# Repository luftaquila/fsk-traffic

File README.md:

# Formula Student Korea Traffic Controller

## Development

### Controller firmware

#### Prerequisites

```sh
git clone https://github.com/luftaquila/fsk-traffic.git
```

* `arm-none-eabi-gcc` ([AArch32 bare-metal target (arm-none-eabi)](https://developer.arm.com/downloads/-/arm-gnu-toolchain-downloads))
* make
* openocd

#### Build and upload

```sh
cd device/firmware
make program
```

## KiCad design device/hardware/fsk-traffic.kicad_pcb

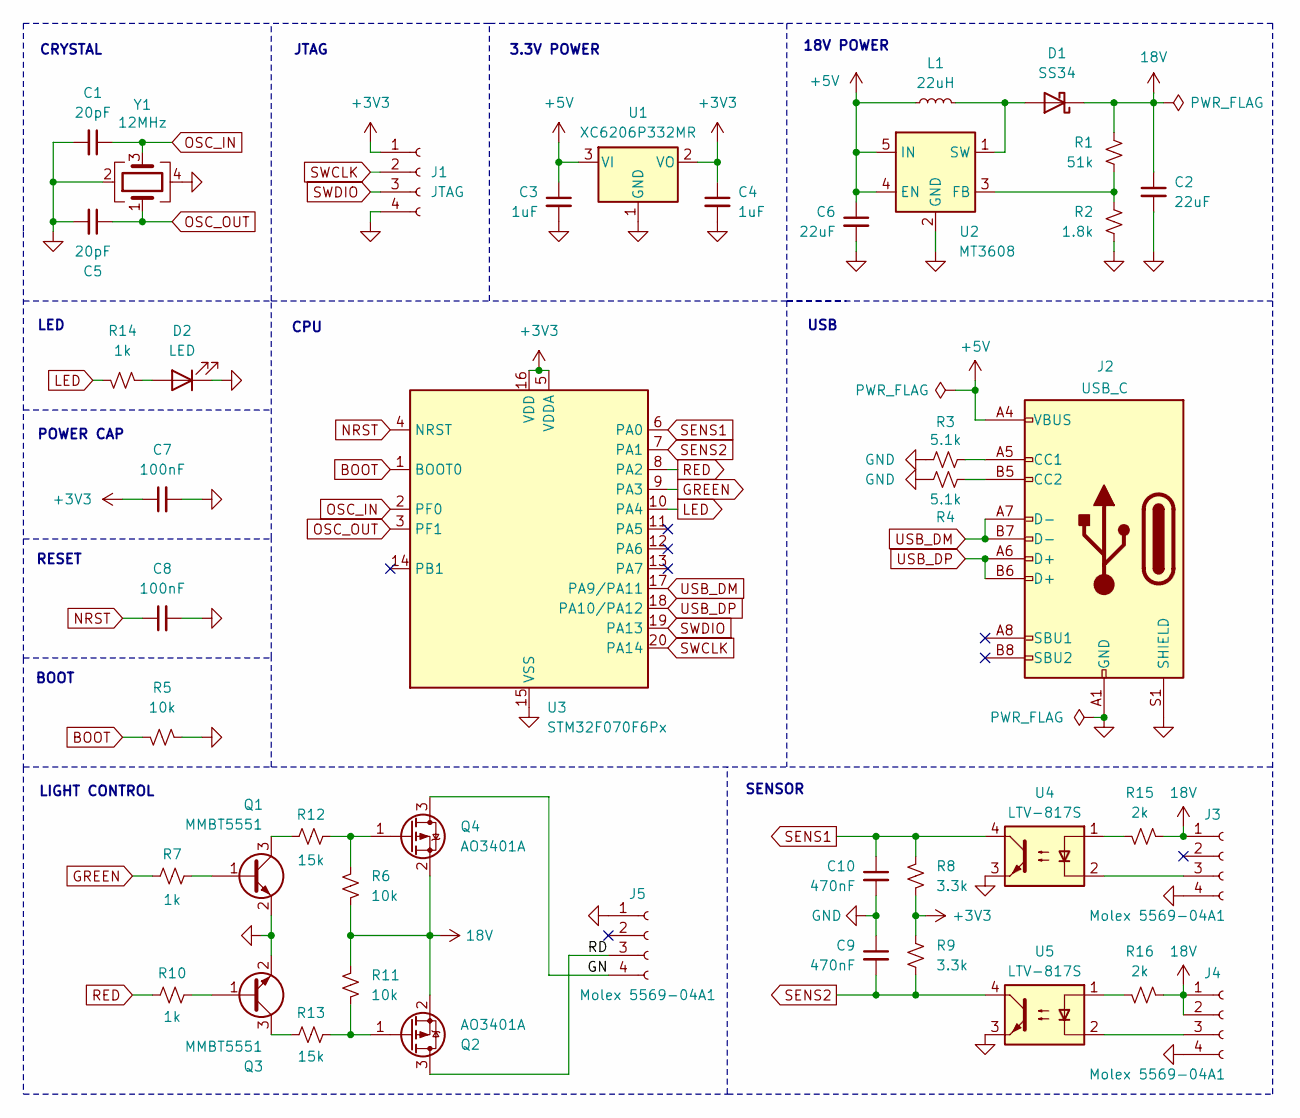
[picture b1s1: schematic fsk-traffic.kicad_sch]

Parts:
C1, C5: 20pF; C_0603_1608Metric; LCSC C1648
C2, C6: 22uF; C_0805_2012Metric; LCSC C45783
C3, C4: 1uF; C_0603_1608Metric; LCSC C15849
C7, C8: 100nF; C_0603_1608Metric; LCSC C14663
C9, C10: 470nF; C_0603_1608Metric; LCSC C1623
D1: SS34; D_SMA; LCSC C8678
D2: LED; LED_0603_1608Metric; LCSC C2286
J1: JTAG; PinHeader_1x04_P2.54mm_Vertical
J2: USB_C; USB_C_Receptacle_GCT_USB4105-xx-A_16P_TopMnt_Horizontal; LCSC C165948
J3, J4, J5: Molex 5569-04A1; Molex_Mini-Fit_Jr_5569-04A1_2x02_P4.20mm_Horizontal
L1: 22uH; L_Changjiang_FXL0630; LCSC C177244
Q1, Q3: MMBT5551; SOT-23; LCSC C2145
Q2, Q4: AO3401A; SOT-23; LCSC C15127
R1: 51k; R_0603_1608Metric; LCSC C23196
R2: 1.8k; R_0603_1608Metric; LCSC C4177
R3, R4: 5.1k; R_0603_1608Metric; LCSC C23186
R5, R6, R11: 10k; R_0603_1608Metric; LCSC C25804
R7, R10, R14: 1k; R_0603_1608Metric; LCSC C21190
R8, R9: 3.3k; R_0603_1608Metric; LCSC C22978
R12, R13: 15k; R_0603_1608Metric; LCSC C22809
R15, R16: 2k; R_0603_1608Metric; LCSC C22975
U1: XC6206P332MR; SOT-23-3; LCSC C5446
U2: MT3608; SOT-23-6; LCSC C2932326
U3: STM32F070F6Px; TSSOP-20_4.4x6.5mm_P0.65mm; LCSC C86951
U4, U5: LTV-817S; SMDIP-4_W9.53mm; LCSC C109227
Y1: 12MHz; Crystal_SMD_3225-4Pin_3.2x2.5mm; LCSC C9002

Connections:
18V: C2.1, D1.1 (K), J3.1, J4.1, J4.2, Q2.2 (S), Q4.2 (S), R1.1, R6.2, R11.1, R15.1, R16.1
+3V3: C4.1, C7.1, J1.1, R8.2, R9.1, U1.2 (VO), U3.5 (VDDA), U3.16 (VDD)
+5V: C3.1, C6.1, J2.A4 (VBUS), J2.A9 (VBUS), J2.B4 (VBUS), J2.B9 (VBUS), L1.1, U1.3 (VI), U2.4 (EN), U2.5 (IN)
/GN: J5.4, Q4.3 (D)
/RD: J5.3, Q2.3 (D)
BOOT: R5.2, U3.1 (BOOT0)
GND: C1.2, C2.2, C3.2, C4.2, C5.2, C6.2, C7.2, C8.2, C9.1, C10.2, D2.1 (K), J1.4, J2.A1 (GND), J2.A12 (GND), J2.B1 (GND), J2.B12 (GND), J2.S1 (SHIELD), J3.4, J4.4, J5.1, Q1.2 (E), Q3.2 (E), R2.2, R3.1, R4.1, R5.1, U1.1 (GND), U2.2 (GND), U3.15 (VSS), U4.3, U5.3, Y1.2, Y1.4
GREEN: R7.2, U3.9 (PA3)
LED: R14.2, U3.10 (PA4)
NRST: C8.1, U3.4 (NRST)
unnamed: D1.2 (A), L1.2, U2.1 (SW)
unnamed: D2.2 (A), R14.1
unnamed: J2.A5 (CC1), R3.2
unnamed: J2.B5 (CC2), R4.2
unnamed: J3.3, U4.2
unnamed: J4.3, U5.2
unnamed: Q1.1 (B), R7.1
unnamed: Q1.3 (C), R12.2
unnamed: Q2.1 (G), R11.2, R13.1
unnamed: Q3.1 (B), R10.1
unnamed: Q3.3 (C), R13.2
unnamed: Q4.1 (G), R6.1, R12.1
unnamed: R15.2, U4.1
unnamed: R16.2, U5.1
unnamed: R1.2, R2.1, U2.3 (FB)
OSC_IN: C1.1, U3.2 (PF0), Y1.3
OSC_OUT: C5.1, U3.3 (PF1), Y1.1
RED: R10.2, U3.8 (PA2)
SENS1: C10.1, R8.1, U3.6 (PA0), U4.4
SENS2: C9.2, R9.2, U3.7 (PA1), U5.4
SWCLK: J1.2, U3.20 (PA14)
SWDIO: J1.3, U3.19 (PA13)
USB_DM: J2.A7 (D-), J2.B7 (D-), U3.17 (PA9/PA11)
USB_DP: J2.A6 (D+), J2.B6 (D+), U3.18 (PA10/PA12)

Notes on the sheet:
SENSOR
3.3V POWER
LIGHT CONTROL
POWER CAP
CPU
JTAG
18V POWER
RESET
BOOT
LED
CRYSTAL
USB

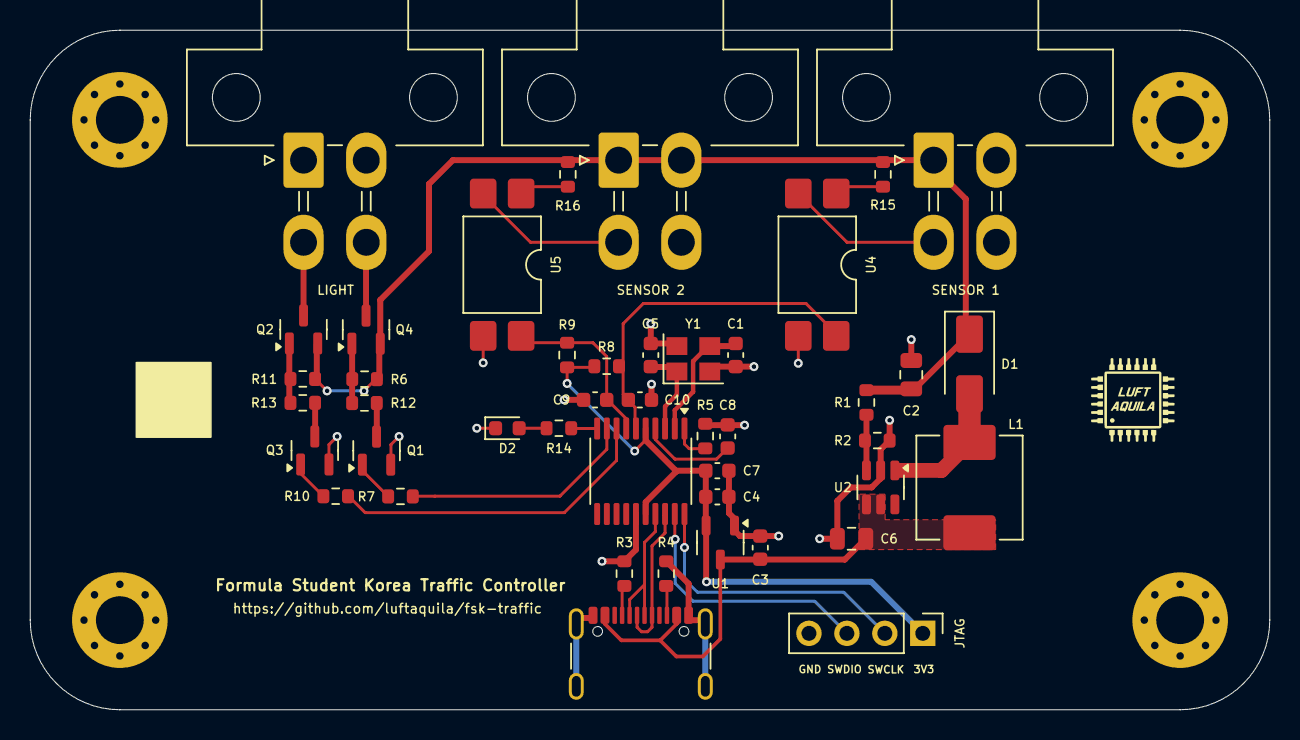
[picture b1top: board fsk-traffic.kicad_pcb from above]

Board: 2 copper layers, 83.0 x 45.5 mm, 44 parts (0 on the bottom side), 34 nets.

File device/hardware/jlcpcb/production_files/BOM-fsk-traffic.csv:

Comment,Designator,Footprint,LCSC,Quantity
LTV-817S,"U4,U5",SMDIP-4_W9.53mm,C109227,2
100nF,"C7,C8",C_0603_1608Metric,C14663,2
AO3401A,"Q2,Q4",SOT-23,C15127,2
1uF,"C3,C4",C_0603_1608Metric,C15849,2
470nF,"C10,C9",C_0603_1608Metric,C1623,2
20pF,"C1,C5",C_0603_1608Metric,C1648,2
USB_C,J2,USB_C_Receptacle_GCT_USB4105-xx-A_16P_TopMnt_Horizontal,C165948,1
22uH,L1,L_Changjiang_FXL0630,C177244,1
1k,"R10,R14,R7",R_0603_1608Metric,C21190,3
MMBT5551,"Q1,Q3",SOT-23,C2145,2
15k,"R12,R13",R_0603_1608Metric,C22809,2
LED,D2,LED_0603_1608Metric,C2286,1
2k,"R15,R16",R_0603_1608Metric,C22975,2
3.3k,"R8,R9",R_0603_1608Metric,C22978,2
5.1k,"R3,R4",R_0603_1608Metric,C23186,2
51k,R1,R_0603_1608Metric,C23196,1
10k,"R11,R5,R6",R_0603_1608Metric,C25804,3
1.8k,R2,R_0603_1608Metric,C4177,1
22uF,"C2,C6",C_0805_2012Metric,C45783,2
XC6206P332MR,U1,SOT-23-3,C5446,1
SS34,D1,D_SMA,C8678,1
STM32F070F6Px,U3,TSSOP-20_4.4x6.5mm_P0.65mm,C86951,1
12MHz,Y1,Crystal_SMD_3225-4Pin_3.2x2.5mm,C9002,1
MT3608,U2,SOT-23-6,,1

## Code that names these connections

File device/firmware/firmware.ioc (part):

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Mcu.Name=STM32F070F6Px
Mcu.Package=TSSOP20
Mcu.UserName=STM32F070F6Px
PA0.GPIOParameters=GPIO_Label,GPIO_ModeDefaultEXTI
PA0.GPIO_Label=SENS1
PA0.GPIO_ModeDefaultEXTI=GPIO_MODE_IT_FALLING
PA0.Signal=GPXTI0
PA1.GPIOParameters=GPIO_Label,GPIO_ModeDefaultEXTI
PA1.GPIO_Label=SENS2
PA1.GPIO_ModeDefaultEXTI=GPIO_MODE_IT_FALLING
PA1.Signal=GPXTI1
PA11.Mode=Device
PA11.Signal=USB_DM
PA12.Mode=Device
PA12.Signal=USB_DP
PA13.Mode=Serial_Wire
PA13.Signal=SYS_SWDIO
PA14.Mode=Serial_Wire
PA14.Signal=SYS_SWCLK
PA2.GPIOParameters=GPIO_Label
PA2.GPIO_Label=RED
PA2.Signal=GPIO_Output
PA3.GPIOParameters=GPIO_Label
PA3.GPIO_Label=GREEN
PA3.Signal=GPIO_Output
PA4.GPIOParameters=GPIO_PuPd,GPIO_Label,GPIO_ModeDefaultOutputPP
PA4.GPIO_Label=LED
PA4.GPIO_ModeDefaultOutputPP=GPIO_MODE_OUTPUT_PP
PA4.GPIO_PuPd=GPIO_NOPULL
PA4.Signal=GPIO_Output
PF0-OSC_IN.Mode=HSE-External-Oscillator
PF0-OSC_IN.Signal=RCC_OSC_IN
PF1-OSC_OUT.Mode=HSE-External-Oscillator
PF1-OSC_OUT.Signal=RCC_OSC_OUT
RCC.HSE_VALUE=12000000
RCC.SYSCLKFreq_VALUE=48000000
RCC.SYSCLKSource=RCC_SYSCLKSOURCE_PLLCLK
board=custom

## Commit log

2025-03-12 remove: sensor firmware
2025-03-16 update: set sensor input pins
2025-03-18 update: new firmware with wired sensors
2025-03-18 fix: make cmds
2025-03-18 improve: fixed length usb cmd
2025-03-18 fix: usb recv flag
2025-03-18 fix: sensor detection bugs
2025-03-18 add: 200ms debouncing
2025-03-23 refactor: UI structure
2025-03-23 fix: misc UI bugs
2025-03-23 impl: main race logic
2025-03-23 update: exclude linux build from release
2025-03-23 impl: save records
2025-03-23 update: readme
2025-03-23 update: beerware license
2025-03-23 add: schematics
2025-04-01 update: match mode name to actual name
2025-04-01 add: skidpad mode UI
2025-04-02 impl: skidpad mode
2025-04-02 add: record save tips
2025-04-05 update: misc style
2025-04-05 update: drop native
2025-04-05 impl: serial handler and POST fetch
2025-04-05 rename: fsk-traffic-control to fsk-traffic
2025-04-05 add: initial server container structure
2025-04-05 impl: server logic
2025-04-07 add: auth user decoder
2025-04-07 add: entry link
2025-04-07 add: docker ci
2025-04-08 update: service port
2025-04-08 improve: replace lowdb to sqlite
2025-04-09 improve: simplify sql queries
2025-04-09 improve: add transaction
2025-05-13 update: replace MCU to STM32F070F6P6
2025-05-13 update: make and openocd script
2025-05-14 add: final PCB and gerber
2025-05-14 update: port application code
2025-06-05 fix: missing pullup on PNP base cause overcurrent
2025-06-05 update: PCB v2
    fix SSR Hi-side driver and MT3608 layout
2025-06-08 fix: add resistor divider to protect PMOS
2025-06-18 fix: misc pcb bugs
2025-09-02 add: pcb workflow
2025-09-02 update: 3d model
2025-09-06 fix: connection error handling
2025-09-08 add: req.body on logs
2025-10-27 fix: isolation & filter
2025-12-25 fix: error handling on device disconnection
2025-12-26 add: housing scad
2025-12-26 fix: missing pcb 18V wiring
2025-12-26 update: remove MT3608 from SMT due to JLC chip misbehavior
2025-12-26 update: latch and engrave depth
